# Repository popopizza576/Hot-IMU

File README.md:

# What is Hot IMU?
The Hot IMU is an IMU based camera tracker that attaches to any hot or cold shoe on a camera and captures its movement. This helps to create dynamic backgrounds using that movement data for compositing green screens instead of static images, which adds a whole new realm of possibilities to what you can do in video post-production and VFX!
### <a href="https://youtu.be/kCqcRCQPGMA">Watch the video here!</a>

# Why use Hot IMU?
The Hot IMU is a great alternative to current Vive-tracker-based solutions for green screen compositing. The Hot IMU does not require any base stations or setup, just put it on and click go, and it will record your motion data.

The Hot IMU is also incredibly affordable compared to the current Vive-tracker-based solutions. It's also extremely affordable, not requiring base stations, which means you can use it virtually anywhere!

# Zine Page

# Assembly
The Hot IMU is a compact ESP-32c3-based device, with a BNO085 IMU and OLED screen. The IMU and OLED screen mount to the PCB with breadboard pins. The battery mounts using a JST 2-pin 1.5mm connector.

### PCB

### Schematic

### BOM

I have created two separate BOMs for my project, because some parts you can't order on Digikey. 

The first BOM plugs into Digikeys' lists and allows you to order things like SMD components for your board.

The second BOM is a list of all additional components you need to buy in order to complete the project.

**You need to buy the contents of BOTH BOMs to build this project!!!**

<a href="https://github.com/popopizza576/Hot-IMU/blob/main/BOM.csv">BOM1</a><br></br>
<a href="https://github.com/popopizza576/Hot-IMU/blob/main/BOM2.csv">BOM2</a>

**PLEASE NOTE**

In addition to purchasing the parts from the BOM, you must have access to a 3D Printer to print the shell for this project.

Also, note that you need to get a quote from a PCB manufacturer of your choosing. **YOU MUST PURCHASE A PCB** The PCB is not included in either BOM.

# Usage
The Hot IMU records movement data to the SD card in CSV format. It records one frame of motion data per frame, and the framerate is specified on the OLED screen.

You can change the framerate by holding down the GO button and pressing the STOP button. The built-in framerates are 24, 30, 60, and 120. the default framerate is 24.

After you've got your CSV file of the motion data recorded, you need to create a Blender scene and find the file path. There is a blender script you need to put in the Scripting tab in Blender.

The Blender Script will parse through the motion data and create an animation of the length of the duration of the data you recorded, then it creates 1 frame of animation for every frame and maps your camera movement to the motion capture.

After you render your Blender animation, just sync up your animation and footage from your camera in your editing software of choice, and key out the background!

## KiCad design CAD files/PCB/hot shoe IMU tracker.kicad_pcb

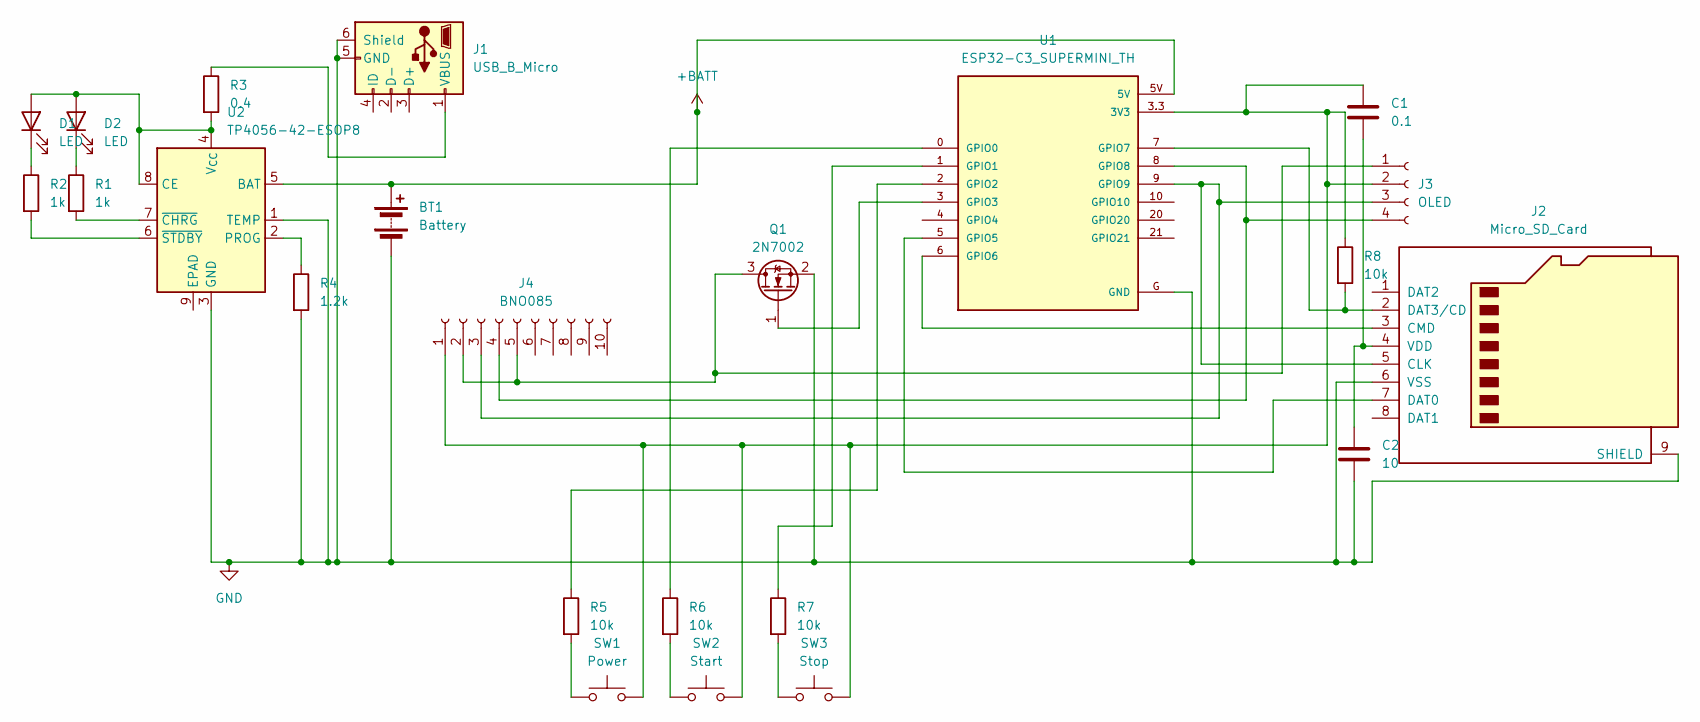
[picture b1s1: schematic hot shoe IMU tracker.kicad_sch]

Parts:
BT1: Battery; JST_ACH_BM02B-ACHSS-GAN-ETF_1x02-1MP_P1.20mm_Vertical
C1: 0.1; C_0402_1005Metric_Pad0.74x0.62mm_HandSolder
C2: 10; C_0402_1005Metric_Pad0.74x0.62mm_HandSolder
D1, D2: LED; LED_0805_2012Metric_Pad1.15x1.40mm_HandSolder
J1: USB_B_Micro; USB_Micro-AB_Molex_47590-0001
J2: Micro_SD_Card; microSD_HC_Molex_104031-0811
J3: OLED; PinHeader_1x04_P1.00mm_Vertical_SMD_Pin1Left
J4: BNO085; PinHeader_1x10_P1.27mm_Vertical_SMD_Pin1Left
Q1: 2N7002; SOT-23
R1, R2: 1k; R_0805_2012Metric_Pad1.20x1.40mm_HandSolder
R3: 0.4; R_0805_2012Metric_Pad1.20x1.40mm_HandSolder
R4: 1.2k; R_0805_2012Metric_Pad1.20x1.40mm_HandSolder
R5, R6, R7, R8: 10k; R_0805_2012Metric_Pad1.20x1.40mm_HandSolder
SW1: Power; SW_DIP_SPSTx01_Slide_6.7x4.1mm_W8.61mm_P2.54mm_LowProfile
SW2: Start; SW_DIP_SPSTx01_Slide_6.7x4.1mm_W8.61mm_P2.54mm_LowProfile
SW3: Stop; SW_DIP_SPSTx01_Slide_6.7x4.1mm_W8.61mm_P2.54mm_LowProfile
U1: ESP32-C3_SUPERMINI_TH; MODULE_ESP32-C3_SUPERMINI
U2: TP4056-42-ESOP8; SOIC-8-1EP_3.9x4.9mm_P1.27mm_EP2.41x3.3mm_ThermalVias

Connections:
+BATT: BT1.1 (+), U1.5V, U2.5 (BAT)
GND: BT1.2 (-), C2.2, J1.5 (GND), J1.6 (Shield), J2.6 (VSS), J2.9 (SHIELD), Q1.2 (S), R4.2, U1.G (GND), U2.1 (TEMP), U2.3 (GND)
unnamed: D1.2 (A), D2.2 (A), R3.2, U2.4 (V_{CC}), U2.8 (CE)
unnamed: D1.1 (K), R2.1
unnamed: D2.1 (K), R1.1
unnamed: J1.1 (VBUS), R3.1
unnamed: J2.5 (CLK), J3.3, J4.3, U1.9 (GPIO9)
unnamed: J2.3 (CMD), U1.6 (GPIO6)
unnamed: J2.7 (DAT0), U1.5 (GPIO5)
unnamed: J2.2 (DAT3/CD), R8.2, U1.7 (GPIO7)
unnamed: C1.2, C2.1, J2.4 (VDD)
unnamed: J3.1, J4.2, J4.5, Q1.3 (D)
unnamed: C1.1, J3.2, J4.1, R8.1, SW1.2, SW2.2, SW3.2, U1.3.3 (3V3)
unnamed: J3.4, J4.4, U1.8 (GPIO8)
unnamed: Q1.1 (G), U1.3 (GPIO3)
unnamed: R5.2, SW1.1
unnamed: R6.2, SW2.1
unnamed: R7.2, SW3.1
unnamed: R6.1, U1.0 (GPIO0)
unnamed: R7.1, U1.1 (GPIO1)
unnamed: R5.1, U1.2 (GPIO2)
unnamed: R4.1, U2.2 (PROG)
unnamed: R1.2, U2.7 (~CHRG)
unnamed: R2.2, U2.6 (~STDBY)

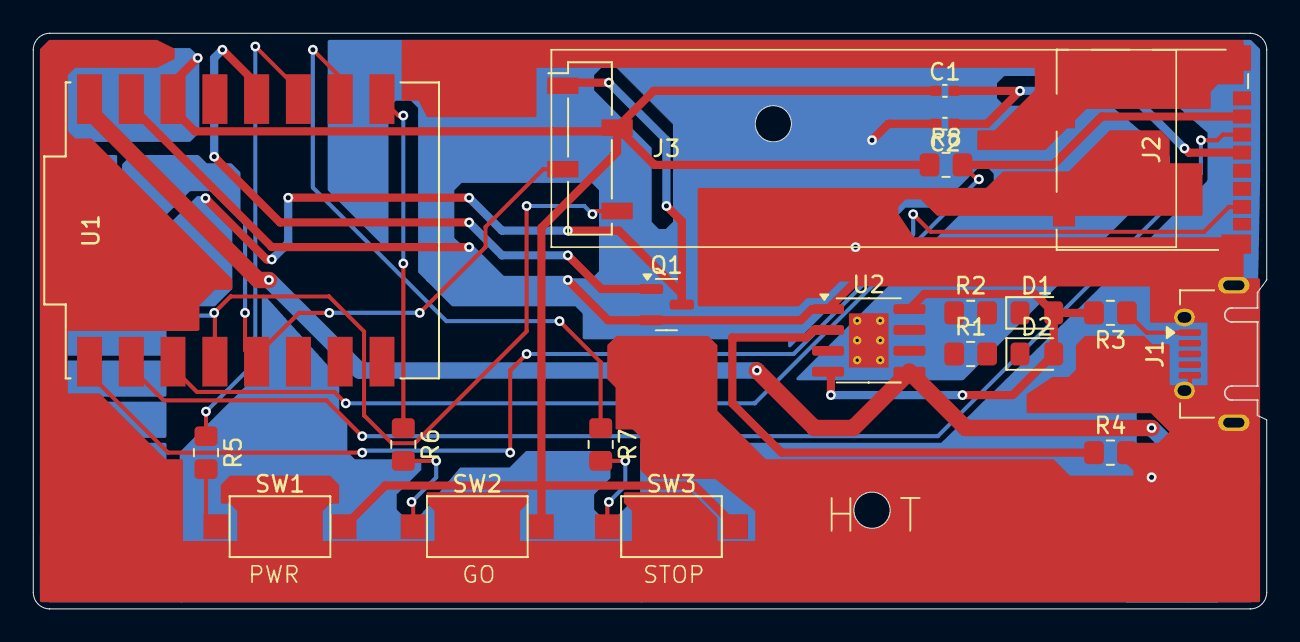
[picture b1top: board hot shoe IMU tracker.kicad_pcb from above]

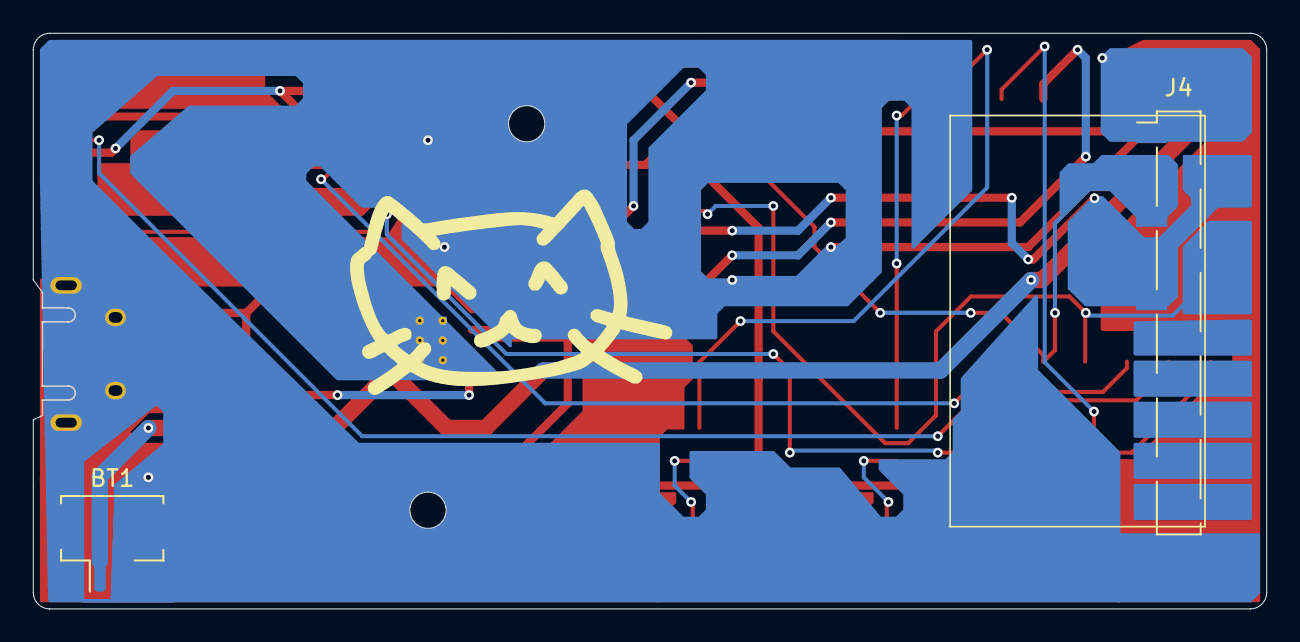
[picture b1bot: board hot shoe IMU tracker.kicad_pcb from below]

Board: 2 copper layers, 75.0 x 35.0 mm, 23 parts (2 on the bottom side), 24 nets.

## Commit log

2026-05-15 Create smth
2026-05-15 Create sn
